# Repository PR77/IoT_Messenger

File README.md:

# IoT_Messenger
IoT Messenger (Pager) For Simple 1 Way Communication

# Warning
This design has not been compliance tested and will not be. It is published purely for inspiration to others. I take no responsibility for damages caused directly or indirectly. I accept no responsibility for any damage to any equipment that results from the use of this design and its components. IT IS ENTIRELY AT YOUR OWN RISK!

# Overview
As a child growing up in the 80's I have fond memories of old skool pagers and analog mobile phones the size of bricks. I remember buying a bunch of old analog Motorola (R) Brick Phones just before the analog network was shut down and turning them into scanners. This project is in no way connected to that, but the fond memory of pagers is something I wanted to bing back with this project. In addition to this, my other motivation for the project was it's "semi" practical use as a real pager within a known WiFi network.

## Basic Concept
My IoT Messenger is essentially some common components connected to an ESP8266, ESP12-F to be specific. However, it is the form factor and user interface which draws parallels to a pager. It is my first revision of the project and has a lot fo fine tuning - should I or the community want to pursue it further. I would like to continue improving this as I see it would be fun for those who use it.

Interfacing with the device is via the Web using the simple HTTP Server class. The IoT Messenger sends out a webpage where the message and other functions can be accessed. As my HTML and JS skills are not up there, I have resorted to using CURL during development and debugging - HELP NEEDED! :)

Here is a nice 3d model of the PCB;

### Appearance
Nice 3D model:

### Basic Interfaces
My IoT Messenger needs to be portable therefore battery power and a basic set of controls are essential. I use a 600 mA LiPo cell which is charged via USB. USB provides power only. No intelligent power management has been implemented yet, so when running only via battery it last 4 - 5 hours.

There are 4 buttons for user input which can also be used for additional functions (see how Tetris and Dino game use them).

### Power Supply
I use the MCP73831 LiPo battery charger with a P-Channel load balancing FET. This is to ensure the LiPo charger only charges the battery when connected to a USB power source. The necessary 3.3 volts is obtained via a basic LM1117-3.3.

### Sensors And Indicators
I wanted to have the PCB somewhat universal - I guess like an evaluation or child friendly development board - so I added a nice RGB LED (PL9823) and an environmental sensor (DHT11). In addition to these, as the device is inspired by pagers, it has a OLED display (128x32) and Piezo Beeper.

As mentioned, flexibility was important so with the OLED, it is essentially dual-footprinted where a module with necessary passives could just be solder on, or the raw OLED panel and necessary passives be soldered on the IoT Messenger board. For my prototype I used the latter so get some experience with this. Lastly, I added a SAO port, well for - Add Ons.

Nice fully soldered IoT Messenger:

### Server
All of the interfacing with the hardware features is via HTTP Server GET and POST requests. The following services have been implemented currently;

|Request |Type|Parameters|Comments                              |
|--------|----|----------|--------------------------------------|
|/list   |GET |none      |Lists files currently saved to SPIFFS |
|/upload |POST|filename  |Uploads a file to SPIFFS              |
|/format |POST|none      |Formats SPIFFS                        |
|/info   |GET |none      |Get SPIFFS and CPU MHz info           |
|/sensor |GET |none      |Read environmental sensor data (DHT11)|
|/message|POST|text      |Write a message to the buffer         |
|/led    |POST|colour    |Set RGB LED colour                    |
|/beeper |POST|count     |Beep piezo beeper                     |

### Fun Stuff
Of course. Check out my IoT Messenger playing the Tetris game theme music or Dino Jump. Videos are in the Images folder.

## Open Sources Used
PlatformIO is the main development environment. In addition to the Arduino framework for ESP8266, I used the following (either important as libraries into PIO or seperate);

1. OLED library (https://github.com/ThingPulse/esp8266-oled-ssd1306)
2. ClickButton library (https://github.com/pkourany/clickButton)
3. RGB LED library (https://github.com/Makuna/NeoPixelBus)
4. Tetris theme song (https://dragaosemchama.com/en/2019/02/songs-for-arduino/)
5. Environmental sensor library (https://github.com/beegee-tokyo/DHTesp)

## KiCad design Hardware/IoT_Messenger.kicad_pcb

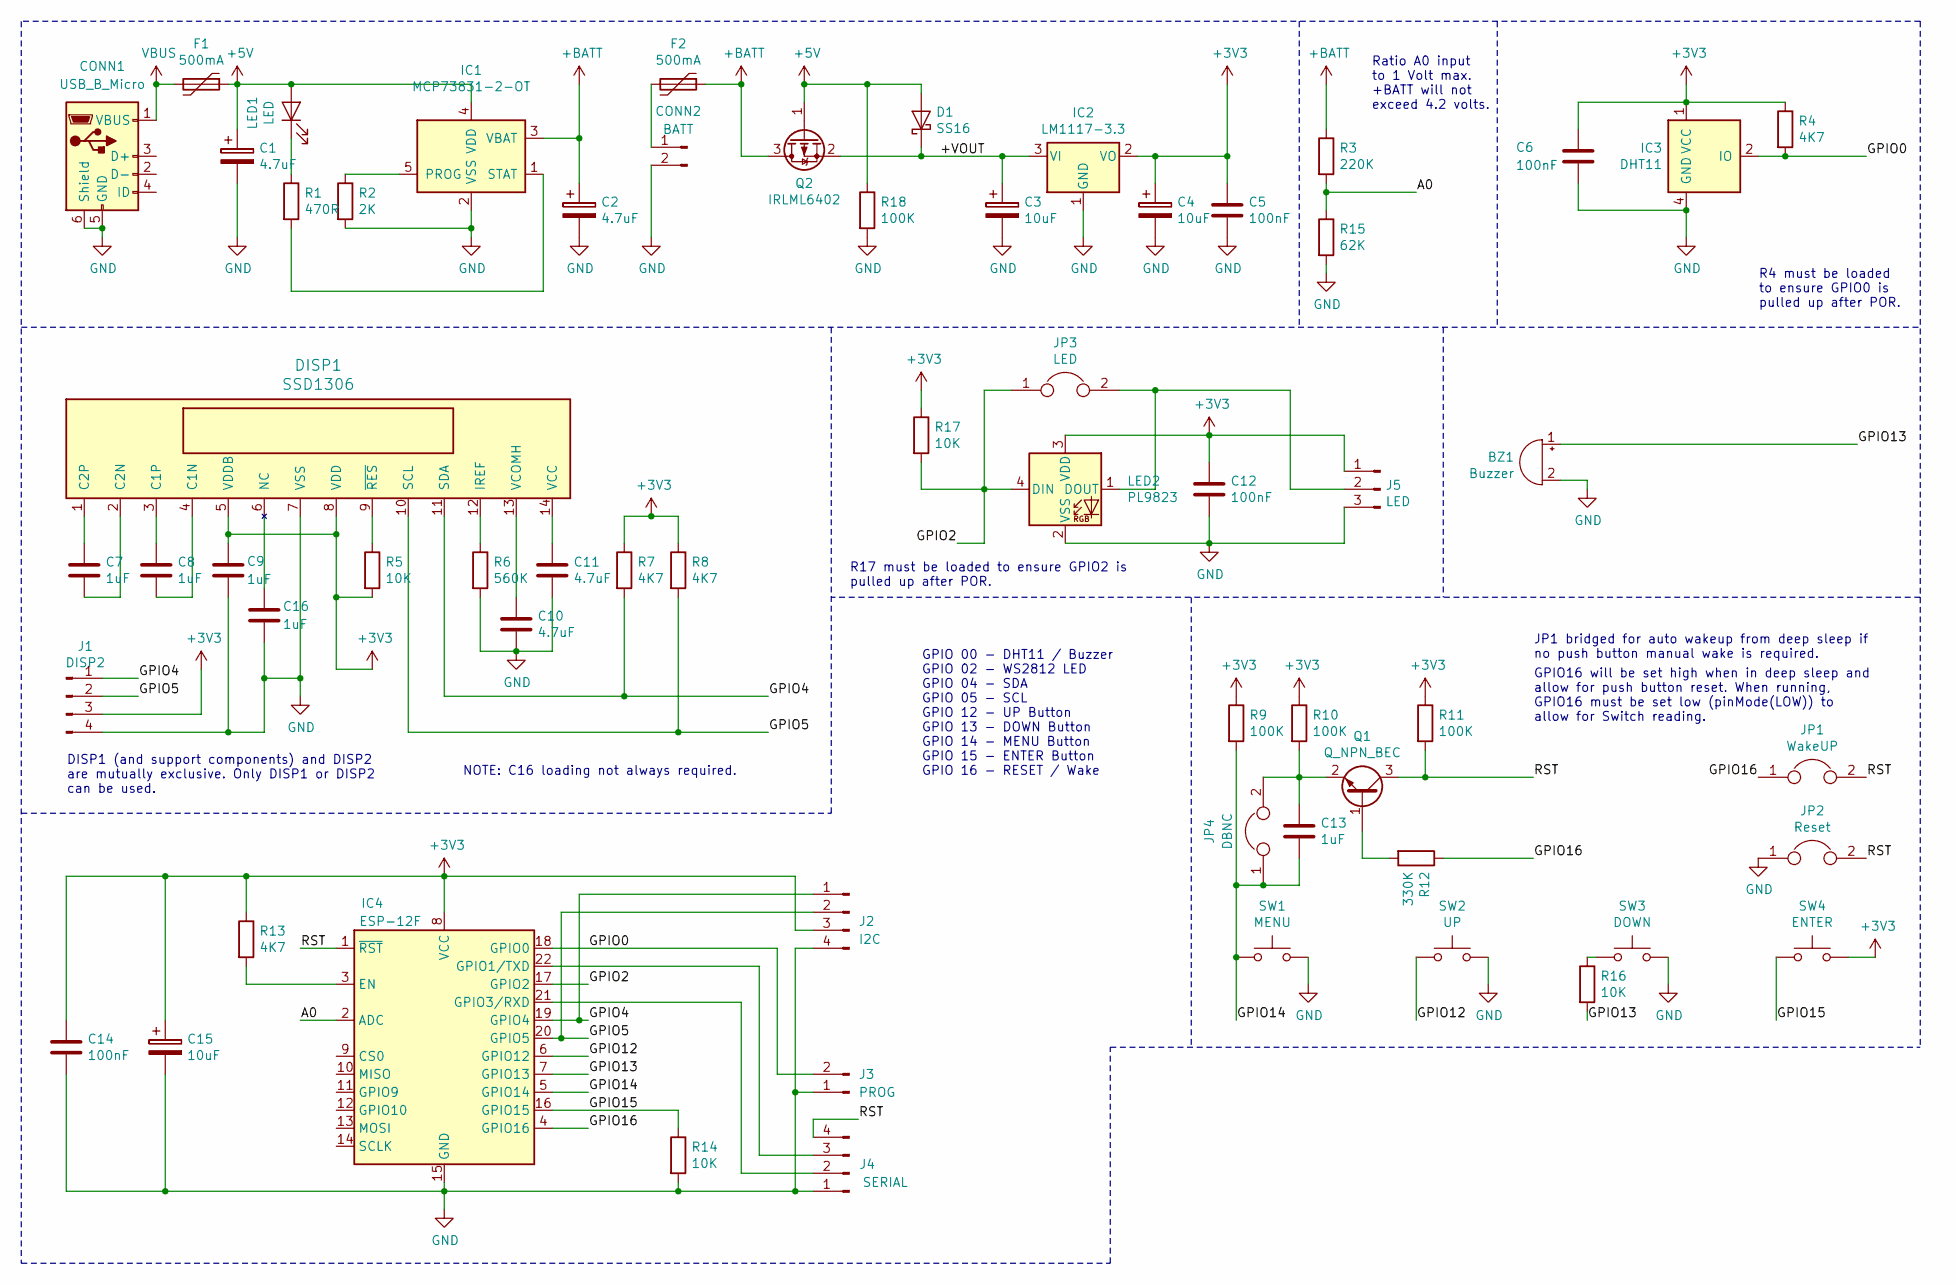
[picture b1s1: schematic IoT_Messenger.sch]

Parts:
BZ1: Buzzer; Buzzer_15x7.5RM7.6
C1, C2: 4.7uF; CP_Tantalum_Case-R_EIA-2012-12_Reflow
C3, C4, C15: 10uF; CP_Tantalum_Case-R_EIA-2012-12_Reflow
C5, C6, C12, C14: 100nF; C_0805
C7, C8, C9, C13, C16: 1uF; C_0805
C10, C11: 4.7uF; C_0805
CONN1: USB_B_Micro; USB_Mini-B
CONN2: BATT; JST_PH_S2B-PH-K_02x2.00mm_Angled
D1: SS16; D_SMA
DISP1: SSD1306; SSD1306_OLED-0.91-128x32
F1, F2: 500mA; Fuse_SMD1206_Reflow
IC1: MCP73831-2-OT; SOT-23-5_HandSoldering
IC2: LM1117-3.3; SOT-223-3_TabPin2
IC3: DHT11; Aosong_DHT11_5.5x12.0_P2.54mm
IC4: ESP-12F; ESP-12E
J1: DISP2; Pin_Header_Straight_1x04_Pitch2.54mm
J2: I2C; Pin_Header_Straight_1x04_Pitch2.54mm
J3: PROG; Pin_Header_Straight_1x02_Pitch2.54mm
J4: SERIAL; Pin_Header_Straight_1x04_Pitch2.54mm
J5: LED; Pin_Header_Straight_1x03_Pitch2.54mm
JP1: WakeUP; SolderJumper-2_P1.3mm_Open_RoundedPad1.0x1.5mm
JP2: Reset; SolderJumper-2_P1.3mm_Open_RoundedPad1.0x1.5mm
JP3: LED; SolderJumper-2_P1.3mm_Open_RoundedPad1.0x1.5mm
JP4: DBNC; SolderJumper-2_P1.3mm_Open_RoundedPad1.0x1.5mm
LED1: LED; LED_0805
LED2: PL9823; LED_D5.0mm-4
Q1: Q_NPN_BEC; SOT-23
Q2: IRLML6402; SOT-23
R1: 470R; R_0805
R2: 2K; R_0805
R3: 220K; R_0805
R4, R7, R8, R13: 4K7; R_0805
R5, R14, R16, R17: 10K; R_0805
R6: 560K; R_0805
R9, R10, R11, R18: 100K; R_0805
R12: 330K; R_0805
R15: 62K; R_0805
SW1: MENU; SW_DIP_x1_W7.62mm_Slide_Copal_CHS-B
SW2: UP; SW_DIP_x1_W7.62mm_Slide_Copal_CHS-B
SW3: DOWN; SW_DIP_x1_W7.62mm_Slide_Copal_CHS-B
SW4: ENTER; SW_DIP_x1_W7.62mm_Slide_Copal_CHS-B

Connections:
+3V3: C4.1, C5.1, C6.1, C9.1, C12.1, C14.1, C15.1, DISP1.5 (VDDB), DISP1.8 (VDD), IC2.2 (VO), IC3.1 (VCC), IC4.8 (VCC), J1.3, J2.3, J5.1, LED2.3 (VDD), R4.1, R5.2, R7.1, R8.1, R9.1, R10.1, R11.1, R13.1, R17.1, SW4.2
+5V: C1.1, D1.2 (A), F1.1, IC1.4 (VDD), LED1.2 (A), Q2.1 (G), R18.1
+BATT: C2.1, F2.1, IC1.3 (VBAT), Q2.3 (D), R3.1
/+VOUT: C3.1, D1.1 (K), IC2.3 (VI), Q2.2 (S)
/A0: IC4.2 (ADC), R3.2, R15.1
/GPIO0: IC3.2 (IO), IC4.18 (GPIO0), J3.2, R4.2
/GPIO2: IC4.17 (GPIO2), JP3.1, LED2.4 (DIN), R17.2
/GPIO4: DISP1.11 (SDA), IC4.19 (GPIO4), J1.1, J2.1, R7.2
/GPIO5: DISP1.10 (SCL), IC4.20 (GPIO5), J1.2, J2.2, R8.2
/GPIO12: IC4.6 (GPIO12), SW2.1
/GPIO13: BZ1.1 (-), IC4.7 (GPIO13), R16.2
/GPIO14: C13.2, IC4.5 (GPIO14), JP4.1, R9.2, SW1.1
/GPIO15: IC4.16 (GPIO15), R14.1, SW4.1
/GPIO16: IC4.4 (GPIO16), JP1.1, R12.1
/RST: IC4.1 (~RST), J4.4, JP1.2, JP2.2, Q1.3 (C), R11.2
GND: BZ1.2 (+), C1.2, C2.2, C3.2, C4.2, C5.2, C6.2, C9.2, C10.2, C11.2, C12.2, C14.2, C15.2, C16.2, CONN1.5 (GND), CONN1.6 (Shield), CONN2.2, DISP1.7 (VSS), IC1.2 (VSS), IC2.1 (GND), IC3.4 (GND), IC4.15 (GND), J1.4, J2.4, J3.1, J4.1, J5.3, JP2.1, LED2.2 (VSS), R2.2, R6.2, R14.2, R15.2, R18.2, SW1.2, SW2.2, SW3.2
unnamed: C7.1, DISP1.1 (C2P)
unnamed: C7.2, DISP1.2 (C2N)
unnamed: C8.1, DISP1.3 (C1P)
unnamed: C8.2, DISP1.4 (C1N)
unnamed: C10.1, DISP1.13 (VCOMH)
unnamed: C11.1, DISP1.14 (VCC)
unnamed: C13.1, JP4.2, Q1.2 (E), R10.2
unnamed: C16.1, DISP1.6 (NC)
unnamed: CONN2.1, F2.2
unnamed: DISP1.9 (~RES), R5.1
unnamed: DISP1.12 (IREF), R6.1
unnamed: IC1.1 (STAT), R1.2
unnamed: IC1.5 (PROG), R2.1
unnamed: IC4.3 (EN), R13.2
unnamed: IC4.21 (GPIO3/RXD), J4.2
unnamed: IC4.22 (GPIO1/TXD), J4.3
unnamed: J5.2, JP3.2, LED2.1 (DOUT)
unnamed: LED1.1 (K), R1.1
unnamed: Q1.1 (B), R12.2
unnamed: R16.1, SW3.1
VBUS: CONN1.1 (VBUS), F1.2

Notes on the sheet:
JP1 bridged for auto wakeup from deep sleep if no push button manual wake is required.
GPIO16 will be set high when in deep sleep and allow for push button reset. When running, GPIO16 must be set low (pinMode(LOW)) to allow for Switch reading.
DISP1 (and support components) and DISP2 are mutually exclusive. Only DISP1 or DISP2 can be used.
GPIO 00 - DHT11 / Buzzer GPIO 02 - WS2812 LED GPIO 04 - SDA GPIO 05 - SCL GPIO 12 - UP Button GPIO 13 - DOWN Button GPIO 14 - MENU Button GPIO 15 - ENTER Button GPIO 16 - RESET / Wake
Ratio A0 input to 1 Volt max. +BATT will not exceed 4.2 volts.
NOTE: C16 loading not always required.
R4 must be loaded to ensure GPIO0 is pulled up after POR.
R17 must be loaded to ensure GPIO2 is pulled up after POR.

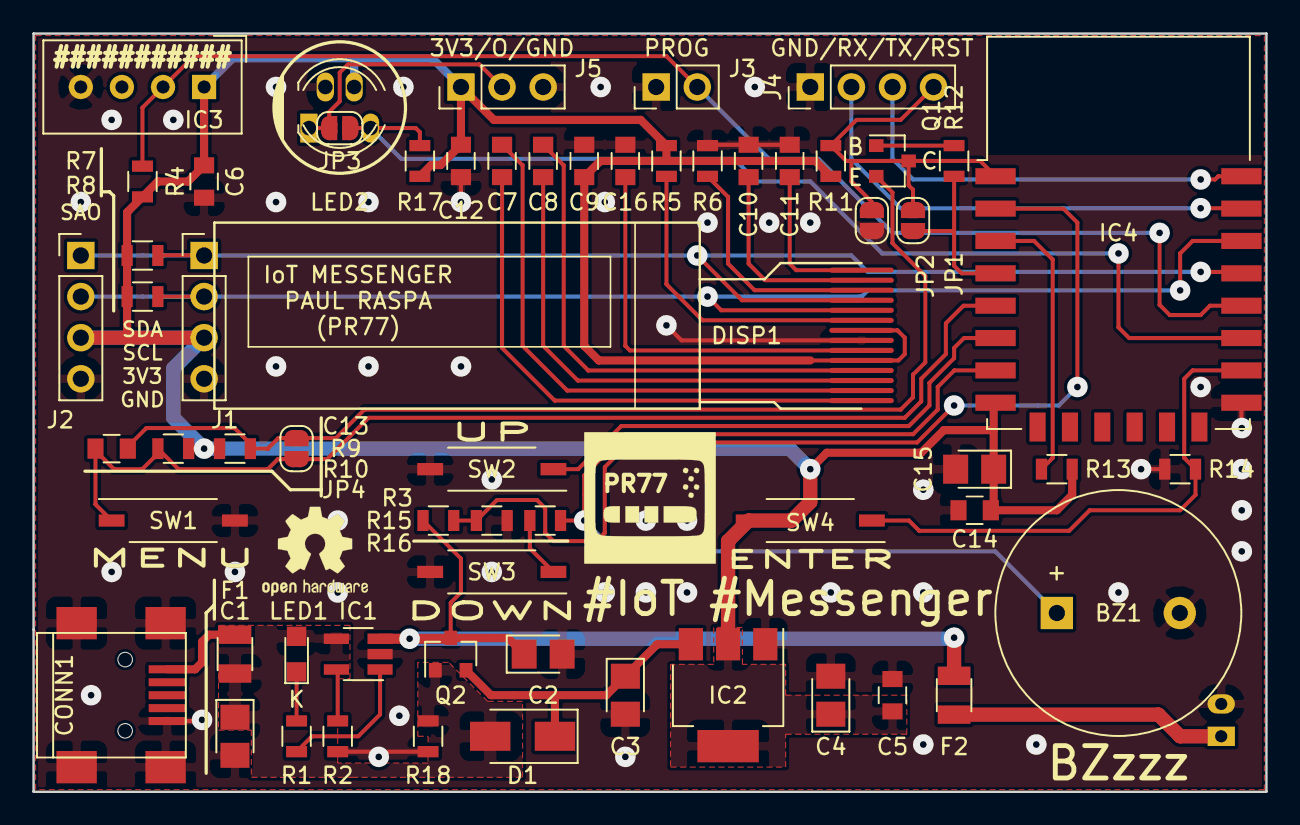
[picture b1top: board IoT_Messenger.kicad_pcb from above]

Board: 2 copper layers, 76.2 x 46.9 mm, 62 parts (1 on the bottom side), 37 nets.

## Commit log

2020-02-24 Updates
    Fixed bug where UI would block during frame skipping recovery.
2020-02-29 Updates
    Inproved Status Frame to show AP IP Address.
2020-04-15 Updates
    Added a Battery Voltage Histogram Frame.
2020-04-21 Updates
    Improved beeper support and better battery histogram
2020-05-04 Updates
    Code refactor
2020-05-04 Updates
    Beeper service supports counts
